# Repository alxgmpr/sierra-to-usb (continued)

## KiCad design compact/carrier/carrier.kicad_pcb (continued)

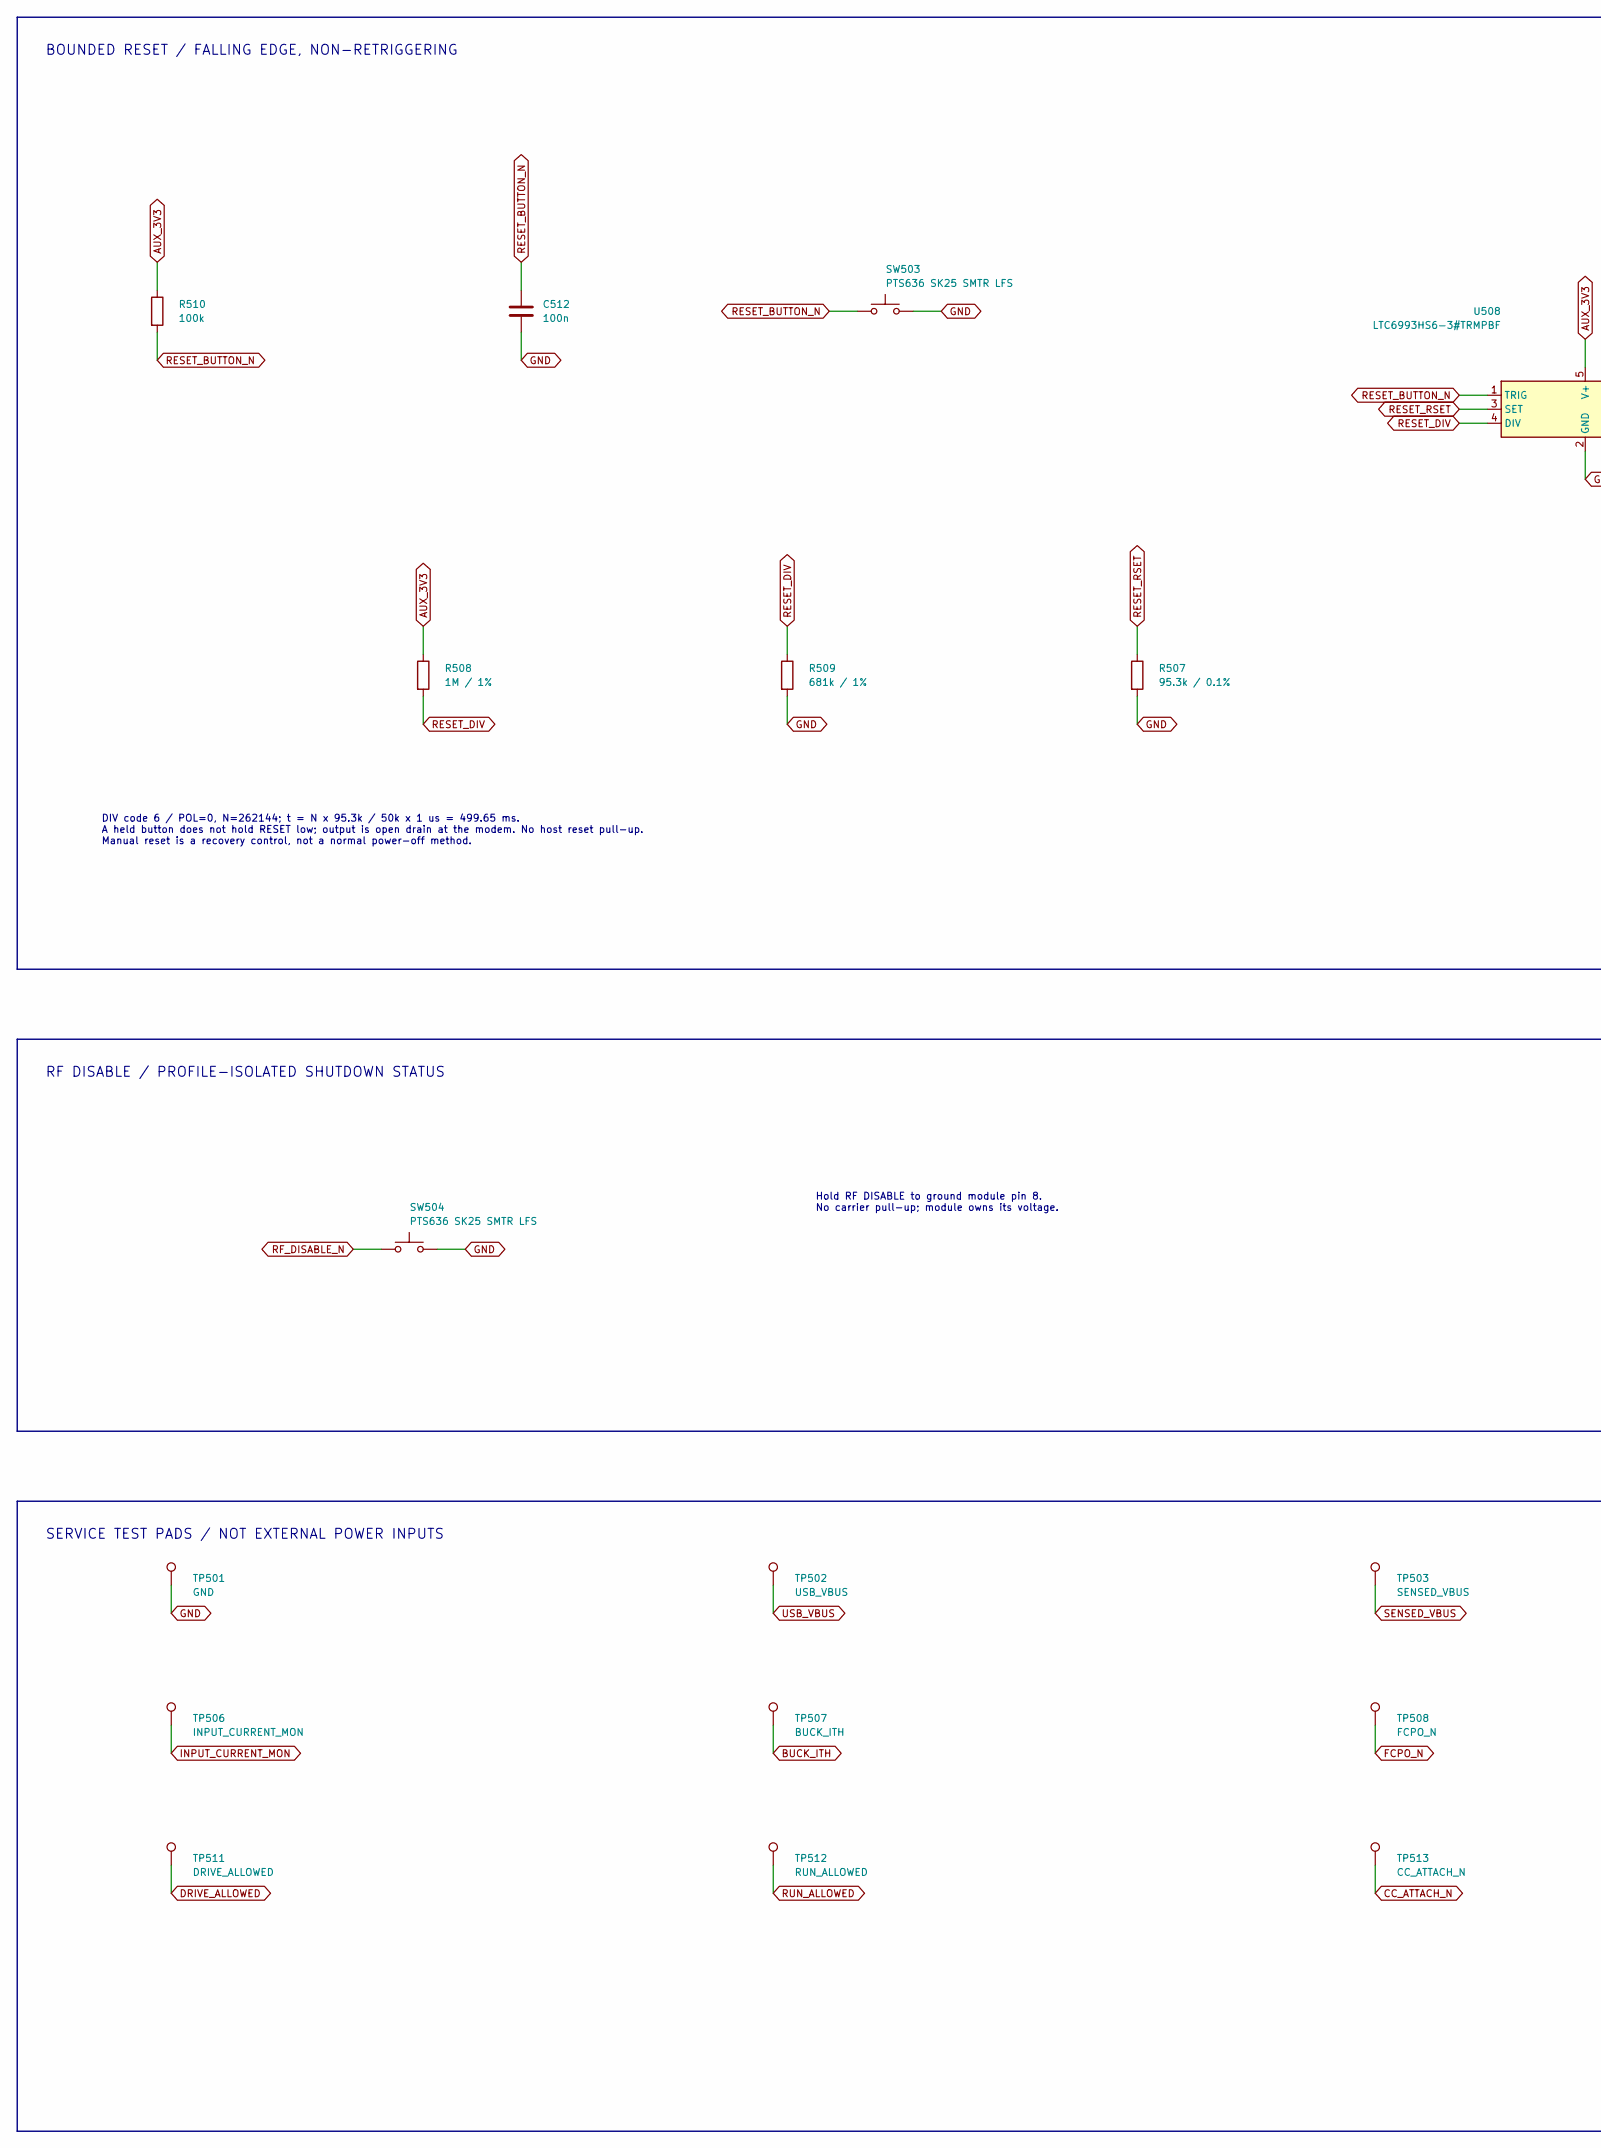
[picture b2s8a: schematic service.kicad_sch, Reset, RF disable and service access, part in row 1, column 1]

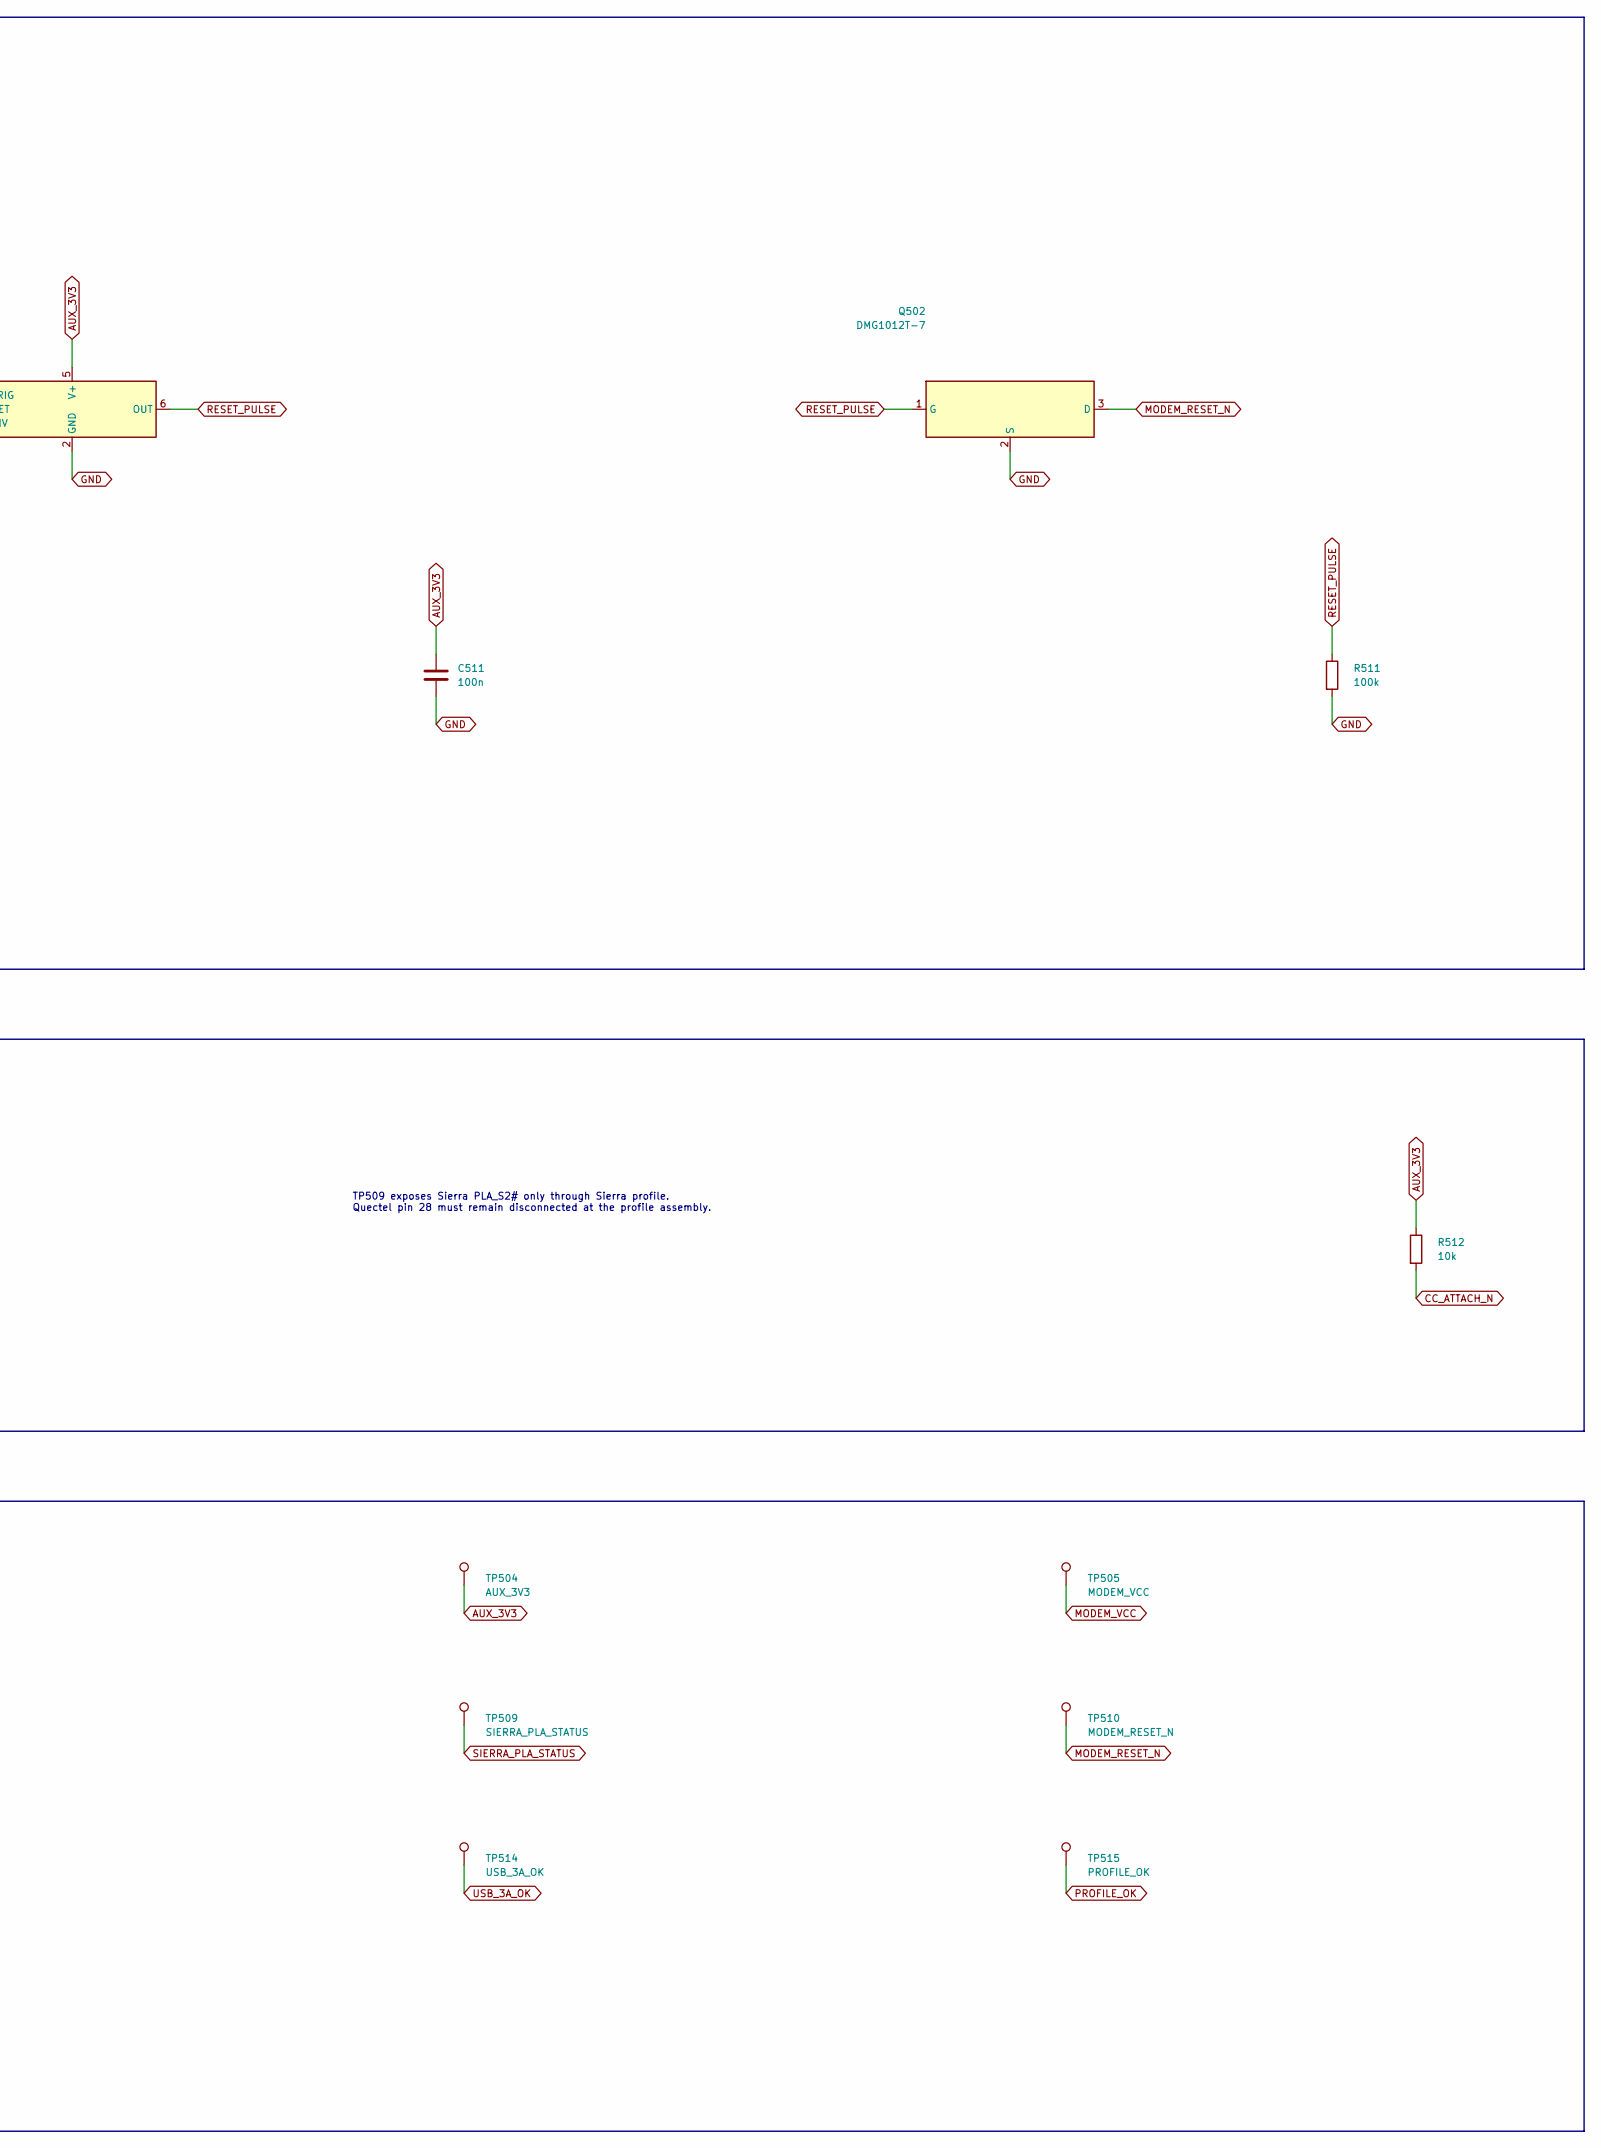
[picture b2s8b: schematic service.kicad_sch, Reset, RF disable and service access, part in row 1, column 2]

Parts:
C511, C512: 100n; C_0805_2012Metric; MPN C2012X7R1H104K085AA
Q502: DMG1012T-7; SOT-523; MPN DMG1012T-7
R507: 95.3k / 0.1%; R_0603_1608Metric; MPN RT0603BRD0795K3L
R508: 1M / 1%; R_0603_1608Metric; MPN RC0603FR-071ML
R509: 681k / 1%; R_0603_1608Metric; MPN RC0603FR-07681KL
R510, R511: 100k; R_0603_1608Metric; MPN RC0603FR-07100KL
R512: 10k; R_0603_1608Metric; MPN RC0603FR-0710KL
SW503, SW504: PTS636 SK25 SMTR LFS; SW_Tactile_SPST_NO_Straight_CK_PTS636Sx25SMTRLFS; MPN PTS636 SK25 SMTR LFS
TP501: GND; TestPoint_Pad_D1.0mm; MPN PCB_TEST_PAD
TP502: USB_VBUS; TestPoint_Pad_D1.0mm; MPN PCB_TEST_PAD
TP503: SENSED_VBUS; TestPoint_Pad_D1.0mm; MPN PCB_TEST_PAD
TP504: AUX_3V3; TestPoint_Pad_D1.0mm; MPN PCB_TEST_PAD
TP505: MODEM_VCC; TestPoint_Pad_D1.0mm; MPN PCB_TEST_PAD
TP506: INPUT_CURRENT_MON; TestPoint_Pad_D1.0mm; MPN PCB_TEST_PAD
TP507: BUCK_ITH; TestPoint_Pad_D1.0mm; MPN PCB_TEST_PAD
TP508: FCPO_N; TestPoint_Pad_D1.0mm; MPN PCB_TEST_PAD
TP509: SIERRA_PLA_STATUS; TestPoint_Pad_D1.0mm; MPN PCB_TEST_PAD
TP510: MODEM_RESET_N; TestPoint_Pad_D1.0mm; MPN PCB_TEST_PAD
TP511: DRIVE_ALLOWED; TestPoint_Pad_D1.0mm; MPN PCB_TEST_PAD
TP512: RUN_ALLOWED; TestPoint_Pad_D1.0mm; MPN PCB_TEST_PAD
TP513: CC_ATTACH_N; TestPoint_Pad_D1.0mm; MPN PCB_TEST_PAD
TP514: USB_3A_OK; TestPoint_Pad_D1.0mm; MPN PCB_TEST_PAD
TP515: PROFILE_OK; TestPoint_Pad_D1.0mm; MPN PCB_TEST_PAD
U508: LTC6993HS6-3#TRMPBF; TSOT-23-6; MPN LTC6993HS6-3#TRMPBF

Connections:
AUX_3V3: C511.1, R508.1, R510.1, R512.1, TP504.1, U508.5 (V+); also elsewhere on the board
BUCK_ITH: TP507.1; also elsewhere on the board
CC_ATTACH_N: R512.2, TP513.1; also elsewhere on the board
DRIVE_ALLOWED: TP511.1; also elsewhere on the board
FCPO_N: TP508.1; also elsewhere on the board
GND: C511.2, C512.2, Q502.2 (S), R507.2, R509.2, R511.2, SW503.2, SW504.2, TP501.1, U508.2 (GND); also elsewhere on the board
INPUT_CURRENT_MON: TP506.1; also elsewhere on the board
MODEM_RESET_N: Q502.3 (D), TP510.1; also elsewhere on the board
MODEM_VCC: TP505.1; also elsewhere on the board
PROFILE_OK: TP515.1; also elsewhere on the board
RESET_BUTTON_N: C512.1, R510.2, SW503.1, U508.1 (TRIG)
RESET_DIV: R508.2, R509.1, U508.4 (DIV)
RESET_PULSE: Q502.1 (G), R511.1, U508.6 (OUT)
RESET_RSET: R507.1, U508.3 (SET)
RF_DISABLE_N: SW504.1; also elsewhere on the board
RUN_ALLOWED: TP512.1; also elsewhere on the board
SENSED_VBUS: TP503.1; also elsewhere on the board
SIERRA_PLA_STATUS: TP509.1; also elsewhere on the board
USB_3A_OK: TP514.1; also elsewhere on the board
USB_VBUS: TP502.1; also elsewhere on the board

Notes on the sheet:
BOUNDED RESET / FALLING EDGE, NON-RETRIGGERING
DIV code 6 / POL=0, N=262144; t = N x 95.3k / 50k x 1 us = 499.65 ms. A held button does not hold RESET low; output is open drain at the modem. No host reset pull-up. Manual reset is a recovery control, not a normal power-off method.
RF DISABLE / PROFILE-ISOLATED SHUTDOWN STATUS
Hold RF DISABLE to ground module pin 8. No carrier pull-up; module owns its voltage.
TP509 exposes Sierra PLA_S2# only through Sierra profile. Quectel pin 28 must remain disconnected at the profile assembly.
SERVICE TEST PADS / NOT EXTERNAL POWER INPUTS

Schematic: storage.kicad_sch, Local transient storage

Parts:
C405, C406, C415, C416: 220u / 6.3V; KEMET_D_7343_Median; MPN T530D227M006ATE005

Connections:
GND: C405.2, C406.2, C415.2, C416.2; also elsewhere on the board
MODEM_VCC: C405.1, C406.1, C415.1, C416.1; also elsewhere on the board

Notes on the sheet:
LOCAL STORAGE / LIVE SOURCE REMAINS CONNECTED
Anode marking faces MODEM_VCC. No series storage switch. The buck supplies the load continuously; these capacitors supply only the temporary difference during a load step.
Bank: 880 uF nominal, 704 uF at -20% initial tolerance. At -20% endurance change: 563.2 uF (before temperature). ESR: 5 mOhm each maximum initially; bank 1.25 mOhm. At 2x endurance ESR: bank 2.5 mOhm (before temperature). These are specified qualification-test limits, not an unlimited lifetime guar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
Local 22 uF ceramics remain on the regulator sheet. Place the polymer bank close to the M.2 VCC distribution, with short, broad supply and return connections. No routing, filled copper or thermal vias are generated.

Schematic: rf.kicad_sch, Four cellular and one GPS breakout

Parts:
J601, J603, J605, J607, J609: 20449-001E-03; IPEX_MHF4_20449_001E_03; MPN 20449-001E-03
J602, J604, J606, J608, J610: 132289; SMA_Amphenol_132289_Manufacturer; MPN 132289

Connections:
GND: J601.2 (Ext), J602.2 (Ext), J603.2 (Ext), J604.2 (Ext), J605.2 (Ext), J606.2 (Ext), J607.2 (Ext), J608.2 (Ext), J609.2 (Ext), J610.2 (Ext); also elsewhere on the board
RF1: J601.1 (In), J602.1 (In)
RF2: J603.1 (In), J604.1 (In)
RF3: J605.1 (In), J606.1 (In)
RF4: J607.1 (In), J608.1 (In)
RF_GPS: J609.1 (In), J610.1 (In)

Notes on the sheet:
FIVE PASSIVE 50 OHM ANTENNA BREAKOUTS
50 ohm PCB launch
RF1..RF4 are neutral port IDs. Connect all four module antennas using four CAB.01072 harnesses. GPS: fifth CAB.01072 only for a dedicated module GNSS port. Sierra mapping: RF1 MAIN / RF2 MIMO1 RF3 MIMO2 / RF4 AUX Quectel mapping: RF1 ANT0 / RF2 ANT1 RF3 ANT2 / RF4 ANT3 No active GNSS bias supply. N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
Coax harnesses terminate at module RF receptacles, not at M.2 edge contacts.

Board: 4 copper layers, 168 parts (0 on the bottom side), 101 nets, no tracks yet.

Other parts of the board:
H1: H1
H2: H2
H3: H3
H4: H4
H5: H5
H10: H10
MECH1: MECH1
